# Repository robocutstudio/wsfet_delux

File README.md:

### Modified FREENFET3 ###

We bought a couple OF Freetronic's FREENFET3 from robotshop but it did not satisfy our electronics connector workflow.
This board is based on the FREENFET3 but offers:
- Four M3 mounting holes
- 3.96mm pitch footprints with a source and drain for each output
-- you can mount screw terminals or MTA-156 connectors or anything else 3.96mm pitch
- 2.54mm pitch for 5v data ground
- power on LED

https://www.freetronics.com.au/products/addressable-triple-n-mosfet-driver-output-module#.W3xziBgnaKo

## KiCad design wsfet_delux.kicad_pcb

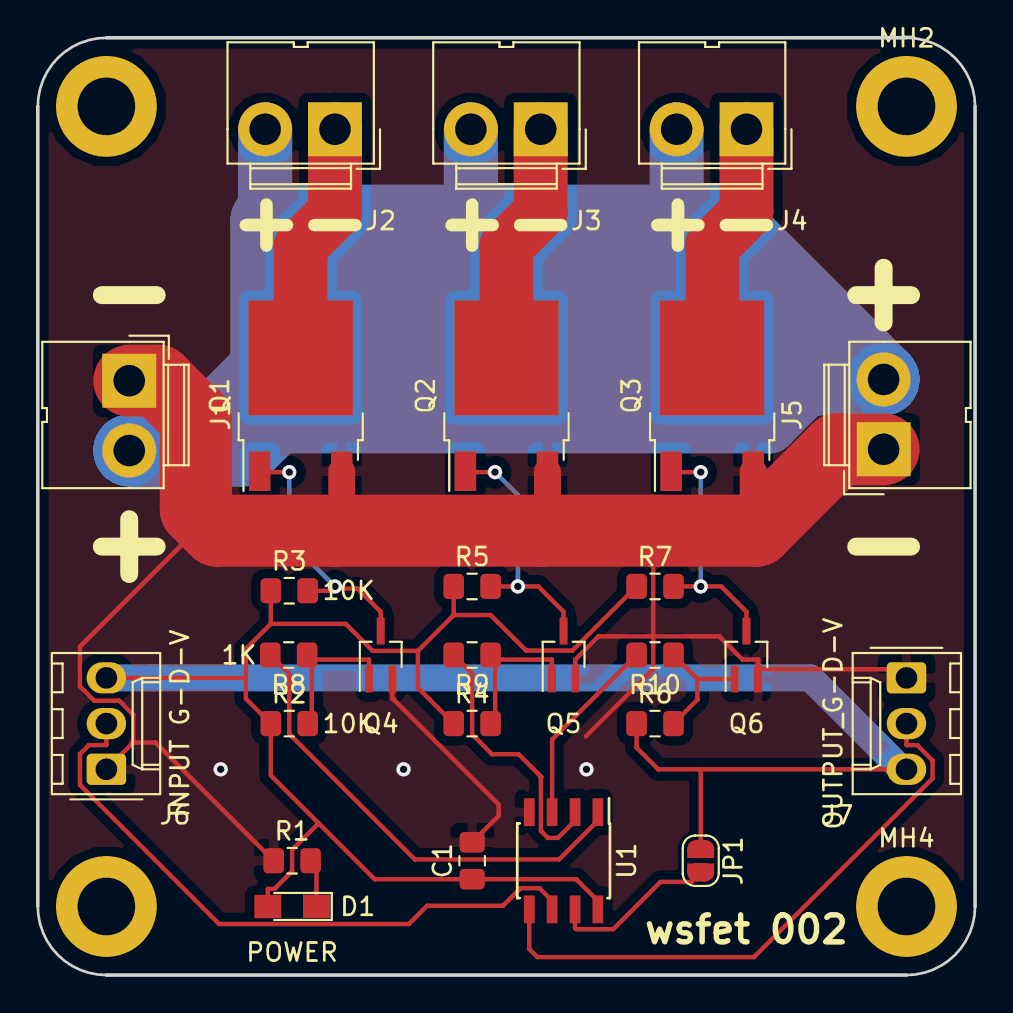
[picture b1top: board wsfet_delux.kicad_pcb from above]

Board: 2 copper layers, 52.1 x 52.1 mm, 31 parts (0 on the bottom side), 19 nets.

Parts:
C1: C; C_0805_2012Metric_Pad1.15x1.40mm_HandSolder
D1: POWER; LED_0805_HandSoldering
J1, J5: JUICE_INPUT; JWT_A3963_1x02_P3.96mm_Vertical
J2: OUT1; JWT_A3963_1x02_P3.96mm_Vertical
J3: OUT2; JWT_A3963_1x02_P3.96mm_Vertical
J4: OUT3; JWT_A3963_1x02_P3.96mm_Vertical
J6: INPUT G-D-V; Molex_KK-254_AE-6410-03A_1x03_P2.54mm_Vertical
J7: OUTPUT_G-D-V; Molex_KK-254_AE-6410-03A_1x03_P2.54mm_Vertical
JP1: Jumper_2_Open; SolderJumper-2_P1.3mm_Open_RoundedPad1.0x1.5mm
MH1, MH2, MH3, MH4: MountingHole_Pad; MountingHole_3.2mm_M3_DIN965_Pad
Q1, Q2, Q3: NTD5867NLT4G; TO-252-2
Q4, Q5, Q6: DMG1012UW-7; SOT-323_SC-70_Handsoldering
R1, R8, R9, R10: 1K; R_0805_2012Metric_Pad1.15x1.40mm_HandSolder
R2, R3, R4, R5, R6, R7: 10K; R_0805_2012Metric_Pad1.15x1.40mm_HandSolder
U1: WS2811; SOIC-8_3.9x4.9mm_P1.27mm

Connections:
/DIN: J6.2, U1.6
/DOUT: J7.2, U1.5
/DRAIN_1: J2.1, Q1.2
/DRAIN_2: J3.1, Q2.2
/DRAIN_3: J4.1, Q3.2
/JUICE: J1.2, J2.2, J3.2, J4.2, J5.2
/OUT1: R8.2, U1.1
/OUT2: R9.2, U1.2
/OUT3: R10.2, U1.3
GND: C1.2, J1.1, J5.1, J6.1, J7.1, Q1.3, Q2.3, Q3.3, Q4.2, Q5.2, Q6.2, R1.1, U1.4
unnamed: D1.1, R1.2
unnamed: JP1.2, U1.7
unnamed: Q1.1, Q4.3, R3.2
unnamed: Q2.1, Q5.3, R5.2
unnamed: Q3.1, Q6.3, R7.2
unnamed: Q4.1, R2.2, R8.1
unnamed: Q5.1, R4.2, R9.1
unnamed: Q6.1, R6.2, R10.1
VCC: C1.1, D1.2, J6.3, J7.3, JP1.1, R2.1, R3.1, R4.1, R5.1, R6.1, R7.1, U1.8

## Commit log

2018-09-05 first comit
2018-09-05 added image
